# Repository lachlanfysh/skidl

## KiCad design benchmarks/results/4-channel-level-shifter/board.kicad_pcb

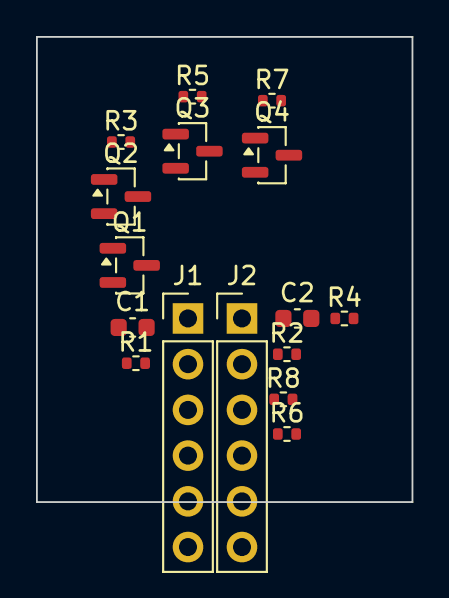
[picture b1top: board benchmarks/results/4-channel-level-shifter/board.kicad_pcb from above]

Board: 2 copper layers, 20.9 x 25.8 mm, 16 parts (0 on the bottom side), 11 nets, no tracks yet.

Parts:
C1, C2: 100nF; C_0603_1608Metric
J1: LV_HDR; PinHeader_1x06_P2.54mm_Vertical
J2: HV_HDR; PinHeader_1x06_P2.54mm_Vertical
Q1, Q2, Q3, Q4: BSS138; SOT-23
R1, R2, R3, R4, R5, R6, R7, R8: 10K; R_0402_1005Metric

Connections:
+3V3: C1.1, J1.6, Q1.1, Q2.1, Q3.1, Q4.1, R1.1, R3.1, R5.1, R7.1
+5V: C2.1, J2.6, R2.1, R4.1, R6.1, R8.1
GND: C1.2, C2.2, J1.1, J2.1
HV1: J2.2, Q1.3, R2.2
HV2: J2.3, Q2.3, R4.2
HV3: J2.4, Q3.3, R6.2
HV4: J2.5, Q4.3, R8.2
LV1: J1.2, Q1.2, R1.2
LV2: J1.3, Q2.2, R3.2
LV3: J1.4, Q3.2, R5.2
LV4: J1.5, Q4.2, R7.2

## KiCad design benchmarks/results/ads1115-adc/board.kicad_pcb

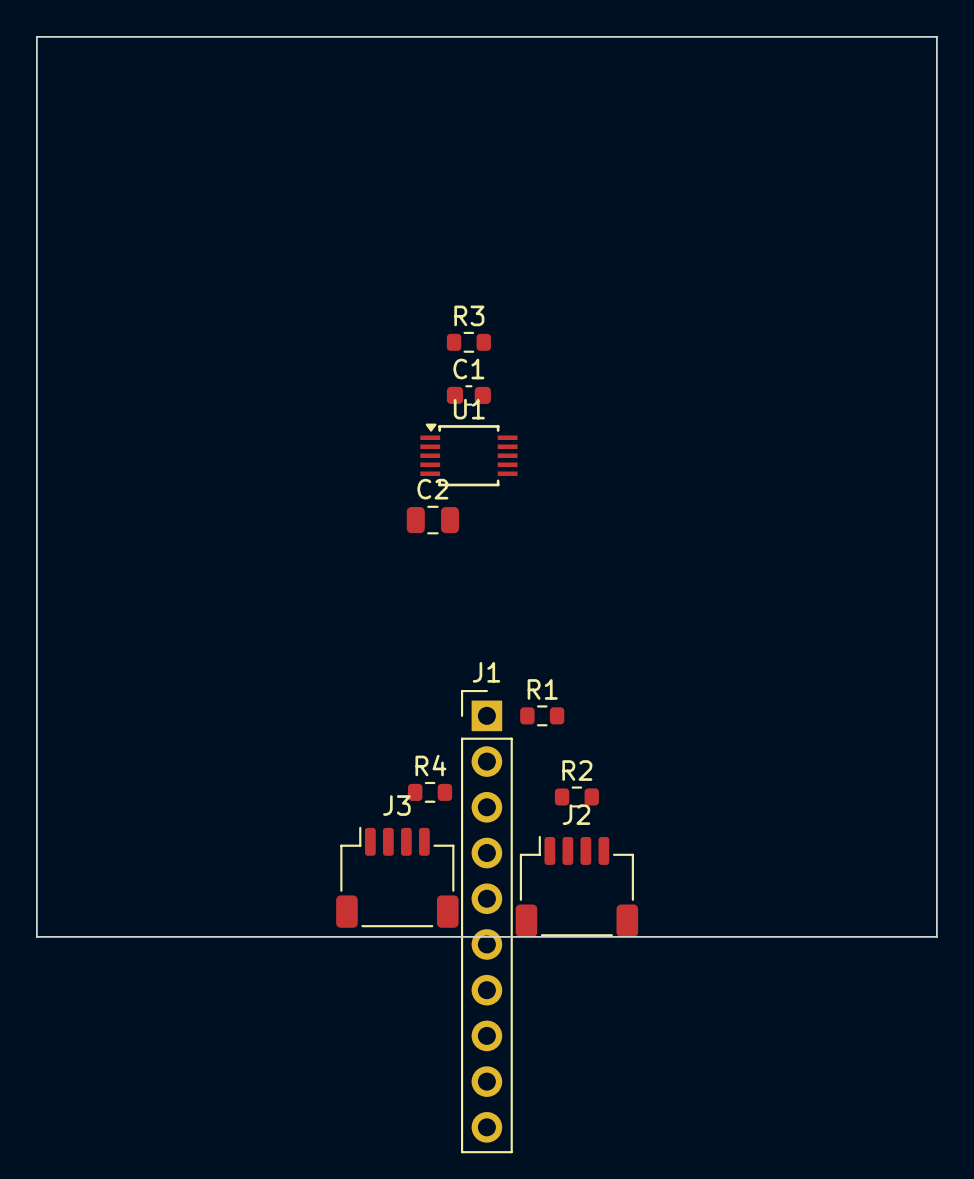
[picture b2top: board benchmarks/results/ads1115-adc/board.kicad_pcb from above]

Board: 2 copper layers, 50.0 x 50.0 mm, 10 parts (0 on the bottom side), 10 nets, no tracks yet.

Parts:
C1: 100nF; C_0603_1608Metric
C2: 10uF; C_0805_2012Metric
J1: Conn_01x10; PinHeader_1x10_P2.54mm_Vertical
J2, J3: Conn_01x04; JST_SH_SM04B-SRSS-TB_1x04-1MP_P1.00mm_Horizontal
R1, R2, R3: 10K; R_0603_1608Metric
R4: 0R; R_0603_1608Metric
U1: ADS1115IDGS; TSSOP-10_3x3mm_P0.5mm

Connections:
ADDR: J1.5, R4.1, U1.1
AIN0: J1.7, U1.4
AIN1: J1.8, U1.5
AIN2: J1.9, U1.6
AIN3: J1.10, U1.7
ALERT_RDY: J1.6, R3.2, U1.2
GND: C1.2, C2.2, J1.2, J2.1, J3.1, R4.2, U1.3
SCL: J1.3, J2.4, J3.4, R2.2, U1.10
SDA: J1.4, J2.3, J3.3, R1.2, U1.9
VDD: C1.1, C2.1, J1.1, J2.2, J3.2, R1.1, R2.1, R3.1, U1.8

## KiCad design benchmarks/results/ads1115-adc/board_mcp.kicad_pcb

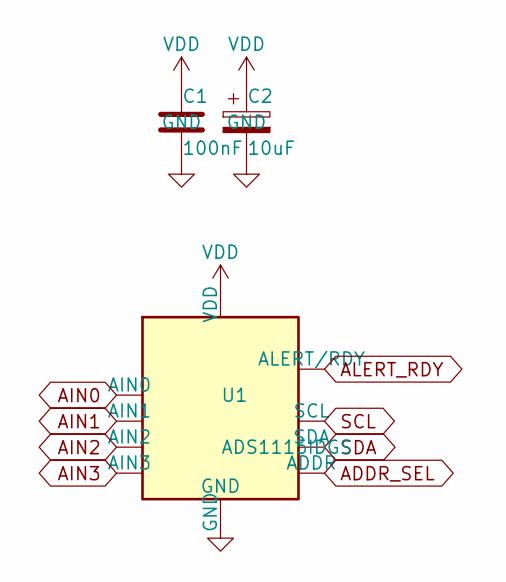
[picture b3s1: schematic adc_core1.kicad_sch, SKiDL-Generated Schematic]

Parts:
C1: 100nF; C_0402_1005Metric
C2: 10uF; C_0805_2012Metric
U1: ADS1115IDGS; TSSOP-10_3x3mm_P0.5mm

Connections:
ADDR_SEL: U1.1 (ADDR); also elsewhere on the board
AIN0: U1.4 (AIN0); also elsewhere on the board
AIN1: U1.5 (AIN1); also elsewhere on the board
AIN2: U1.6 (AIN2); also elsewhere on the board
AIN3: U1.7 (AIN3); also elsewhere on the board
ALERT_RDY: U1.2 (ALERT/RDY); also elsewhere on the board
GND: C1.2, C2.2, U1.3 (GND); also elsewhere on the board
SCL: U1.10 (SCL); also elsewhere on the board
SDA: U1.9 (SDA); also elsewhere on the board
VDD: C1.1, C2.1, U1.8 (VDD); also elsewhere on the board

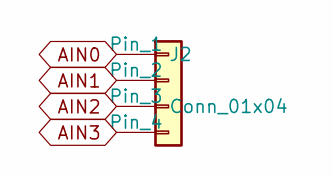
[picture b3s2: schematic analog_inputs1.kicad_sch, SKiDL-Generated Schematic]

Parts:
J2: Conn_01x04; PinHeader_1x04_P2.54mm_Vertical

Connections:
AIN0: J2.1; also elsewhere on the board
AIN1: J2.2; also elsewhere on the board
AIN2: J2.3; also elsewhere on the board
AIN3: J2.4; also elsewhere on the board

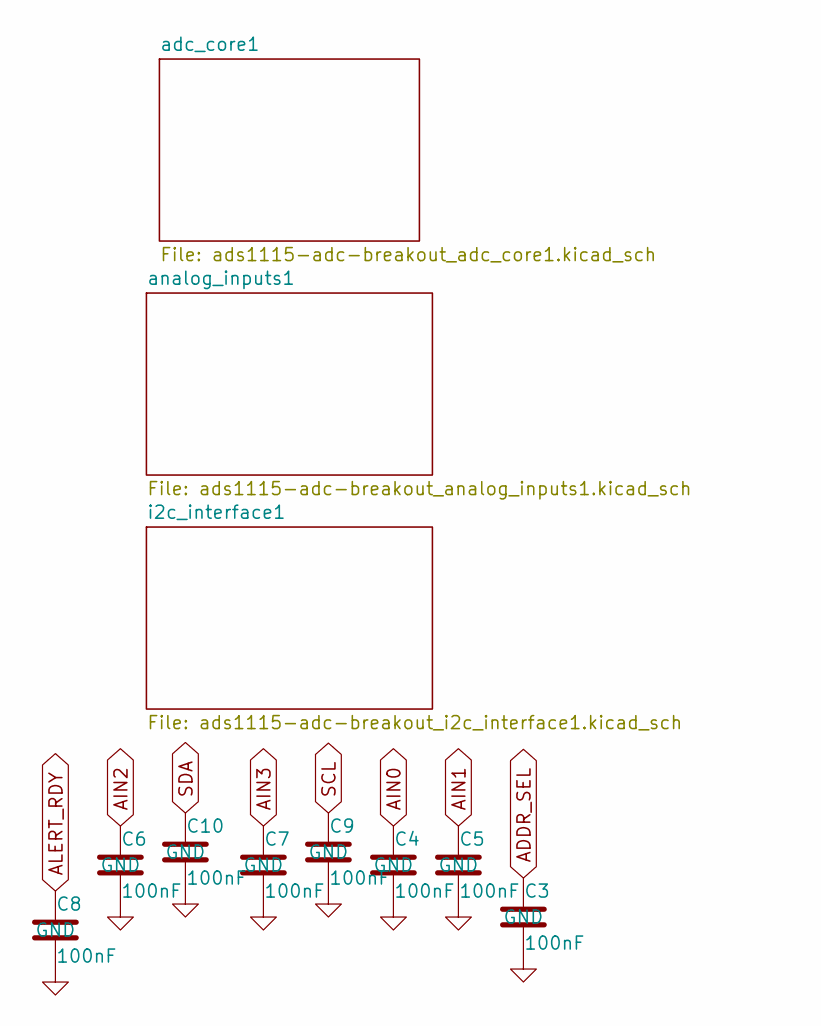
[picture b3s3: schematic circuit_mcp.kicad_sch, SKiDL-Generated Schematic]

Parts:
C3, C4, C5, C6, C7, C8, C9, C10: 100nF; C_0603_1608Metric

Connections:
ADDR_SEL: C3.1; also elsewhere on the board
AIN0: C4.1; also elsewhere on the board
AIN1: C5.1; also elsewhere on the board
AIN2: C6.1; also elsewhere on the board
AIN3: C7.1; also elsewhere on the board
ALERT_RDY: C8.1; also elsewhere on the board
GND: C3.2, C4.2, C5.2, C6.2, C7.2, C8.2, C9.2, C10.2; also elsewhere on the board
SCL: C9.1; also elsewhere on the board
SDA: C10.1; also elsewhere on the board

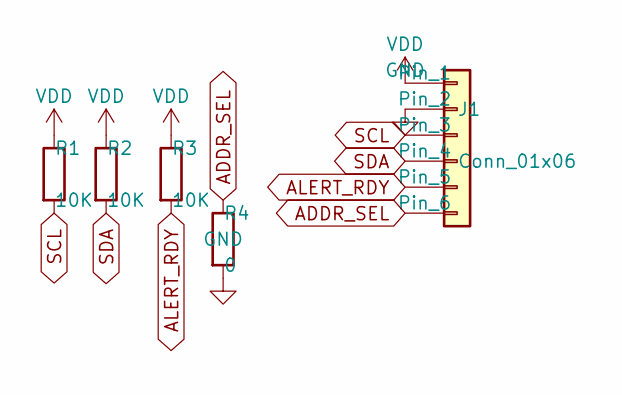
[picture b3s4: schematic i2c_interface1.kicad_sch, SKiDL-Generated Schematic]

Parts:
J1: Conn_01x06; PinHeader_1x06_P2.54mm_Vertical
R1, R2, R3: 10K; R_0402_1005Metric
R4: 0; R_0402_1005Metric

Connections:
ADDR_SEL: J1.6, R4.1; also elsewhere on the board
ALERT_RDY: J1.5, R3.2; also elsewhere on the board
GND: J1.2, R4.2; also elsewhere on the board
SCL: J1.3, R1.2; also elsewhere on the board
SDA: J1.4, R2.2; also elsewhere on the board
VDD: J1.1, R1.1, R2.1, R3.1; also elsewhere on the board

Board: 2 copper layers, 17 parts (0 on the bottom side), 10 nets, no tracks yet.

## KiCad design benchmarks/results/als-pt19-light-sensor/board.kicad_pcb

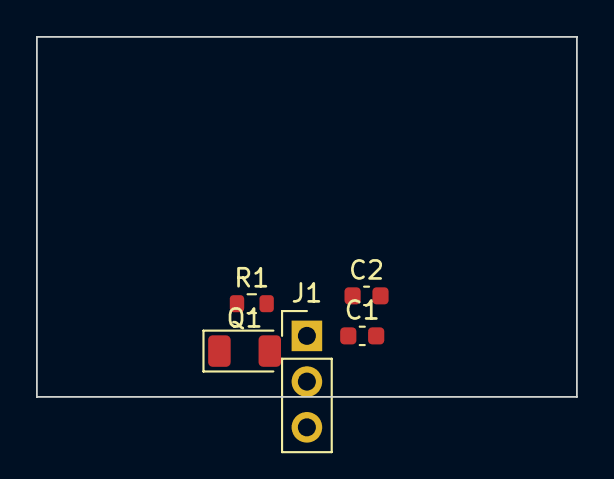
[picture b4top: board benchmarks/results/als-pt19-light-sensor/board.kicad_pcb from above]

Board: 2 copper layers, 30.0 x 20.0 mm, 5 parts (0 on the bottom side), 3 nets, no tracks yet.

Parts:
C1, C2: 100nF; C_0603_1608Metric
J1: Conn_01x03; PinHeader_1x03_P2.54mm_Vertical
Q1: ALS-PT19; LED_1206_3216Metric
R1: 10K; R_0603_1608Metric

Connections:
AOUT: C2.1, J1.3
GND: C1.2, C2.2, J1.2, Q1.2
VCC: C1.1, J1.1, R1.1

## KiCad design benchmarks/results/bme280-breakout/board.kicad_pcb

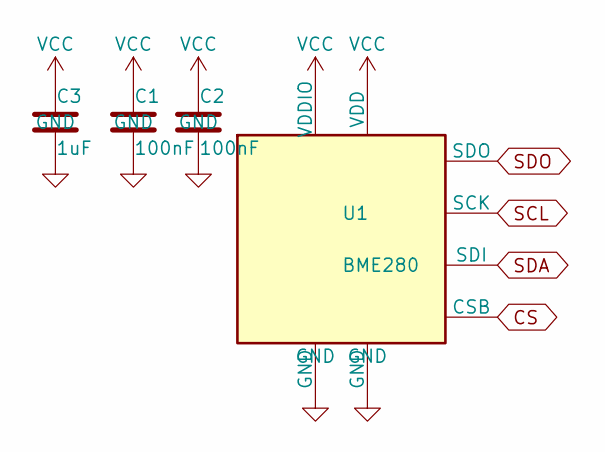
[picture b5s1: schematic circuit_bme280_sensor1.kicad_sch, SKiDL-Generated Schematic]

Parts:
C1, C2: 100nF; C_0402_1005Metric
C3: 1uF; C_0402_1005Metric
U1: BME280; Bosch_LGA-8_2.5x2.5mm_P0.65mm_ClockwisePinNumbering

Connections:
CS: U1.2 (CSB); also elsewhere on the board
GND: C1.2, C2.2, C3.2, U1.1 (GND), U1.7 (GND); also elsewhere on the board
SCL: U1.4 (SCK); also elsewhere on the board
SDA: U1.3 (SDI); also elsewhere on the board
SDO: U1.5 (SDO); also elsewhere on the board
VCC: C1.1, C2.1, C3.1, U1.6 (VDDIO), U1.8 (VDD); also elsewhere on the board

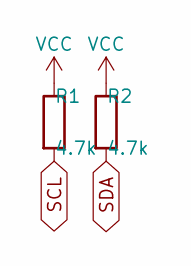
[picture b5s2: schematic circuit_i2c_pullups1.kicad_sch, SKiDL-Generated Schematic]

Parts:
R1, R2: 4.7k; R_0402_1005Metric

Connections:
SCL: R1.2; also elsewhere on the board
SDA: R2.2; also elsewhere on the board
VCC: R1.1, R2.1; also elsewhere on the board

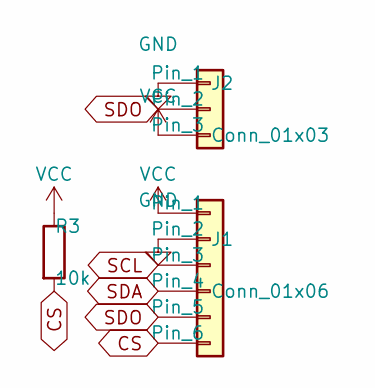
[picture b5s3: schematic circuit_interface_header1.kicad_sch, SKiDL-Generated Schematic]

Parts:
J1: Conn_01x06; PinHeader_1x06_P2.54mm_Vertical
J2: Conn_01x03; PinHeader_1x03_P2.54mm_Vertical
R3: 10k; R_0402_1005Metric

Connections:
CS: J1.6, R3.2; also elsewhere on the board
GND: J1.2, J2.1; also elsewhere on the board
SCL: J1.3; also elsewhere on the board
SDA: J1.4; also elsewhere on the board
SDO: J1.5, J2.2; also elsewhere on the board
VCC: J1.1, J2.3, R3.1; also elsewhere on the board

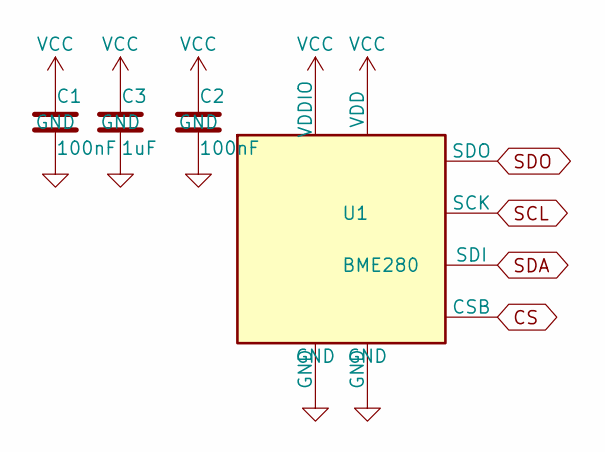
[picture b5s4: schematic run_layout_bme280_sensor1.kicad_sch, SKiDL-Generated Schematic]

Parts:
C1, C2: 100nF; C_0402_1005Metric
C3: 1uF; C_0402_1005Metric
U1: BME280; Bosch_LGA-8_2.5x2.5mm_P0.65mm_ClockwisePinNumbering

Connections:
CS: U1.2 (CSB); also elsewhere on the board
GND: C1.2, C2.2, C3.2, U1.1 (GND), U1.7 (GND); also elsewhere on the board
SCL: U1.4 (SCK); also elsewhere on the board
SDA: U1.3 (SDI); also elsewhere on the board
SDO: U1.5 (SDO); also elsewhere on the board
VCC: C1.1, C2.1, C3.1, U1.6 (VDDIO), U1.8 (VDD); also elsewhere on the board

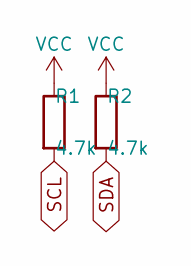
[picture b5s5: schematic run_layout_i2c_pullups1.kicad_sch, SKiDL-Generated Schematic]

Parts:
R1, R2: 4.7k; R_0402_1005Metric

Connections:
SCL: R1.2; also elsewhere on the board
SDA: R2.2; also elsewhere on the board
VCC: R1.1, R2.1; also elsewhere on the board

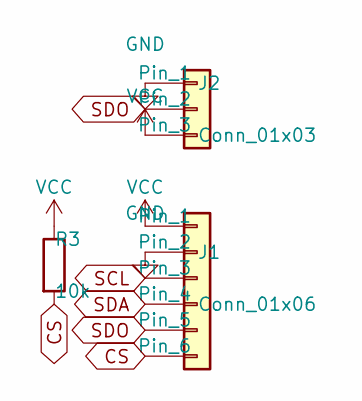
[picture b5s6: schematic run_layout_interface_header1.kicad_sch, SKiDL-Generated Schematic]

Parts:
J1: Conn_01x06; PinHeader_1x06_P2.54mm_Vertical
J2: Conn_01x03; PinHeader_1x03_P2.54mm_Vertical
R3: 10k; R_0402_1005Metric

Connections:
CS: J1.6, R3.2; also elsewhere on the board
GND: J1.2, J2.1; also elsewhere on the board
SCL: J1.3; also elsewhere on the board
SDA: J1.4; also elsewhere on the board
SDO: J1.5, J2.2; also elsewhere on the board
VCC: J1.1, J2.3, R3.1; also elsewhere on the board

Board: 2 copper layers, 9 parts (0 on the bottom side), 6 nets, no tracks yet.

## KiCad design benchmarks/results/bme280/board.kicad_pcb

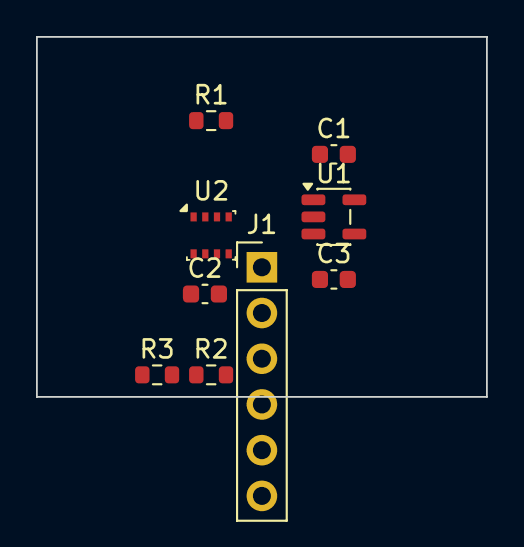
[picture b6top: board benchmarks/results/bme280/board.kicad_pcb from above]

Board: 2 copper layers, 25.0 x 20.0 mm, 9 parts (0 on the bottom side), 7 nets, no tracks yet.

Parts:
C1, C2: 1uF; C_0603_1608Metric
C3: 100nF; C_0603_1608Metric
J1: Header_1x06; PinHeader_1x06_P2.54mm_Vertical
R1, R2, R3: 10K; R_0603_1608Metric
U1: AP2112K-3.3; SOT-23-5
U2: BME280; Bosch_LGA-8_2.5x2.5mm_P0.65mm_ClockwisePinNumbering

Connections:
+3V3: C2.1, C3.1, R1.1, R2.1, R3.1, U1.5, U2.6, U2.8
CSB: J1.6, R3.2, U2.2
GND: C1.2, C2.2, C3.2, J1.2, U1.2, U2.1, U2.7
SCL: J1.3, R2.2, U2.4
SDA: J1.4, R1.2, U2.3
SDO: J1.5, U2.5
VIN: C1.1, J1.1, U1.1, U1.3

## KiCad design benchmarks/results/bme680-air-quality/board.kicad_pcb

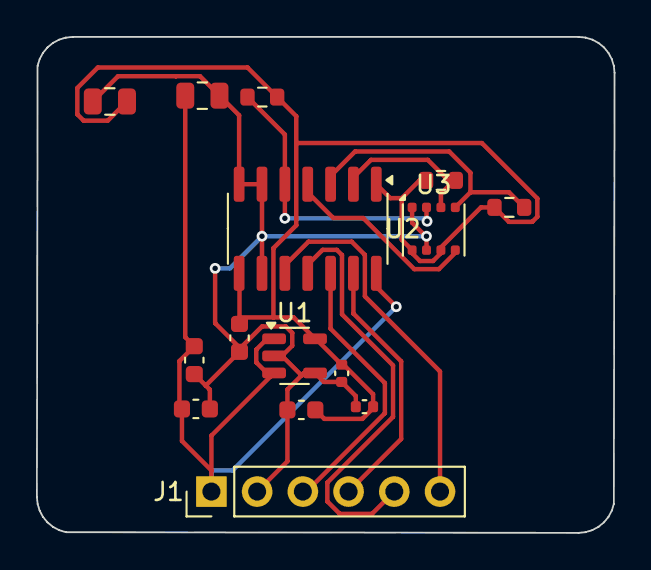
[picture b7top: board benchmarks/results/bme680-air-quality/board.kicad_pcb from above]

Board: 2 copper layers, 32.1 x 27.6 mm, 15 parts (0 on the bottom side), 11 nets.

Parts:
C1: 1uF; C_0603_1608Metric
C2, C8: 10uF; C_0805_2012Metric
C3, C4, C5: 100nF; C_0603_1608Metric
C6, C7: 100nF; C_0402_1005Metric
J1: Conn_01x06; PinHeader_1x06_P2.54mm_Vertical
R1, R2: 4.7K; R_0603_1608Metric
R3: 10K; R_0603_1608Metric
U1: AP2112K-3.3; SOT-23-5
U2: TXB0104D; SOIC-14_3.9x8.7mm_P1.27mm
U3: BME680; Bosch_LGA-8_3x3mm_P0.8mm_ClockwisePinNumbering

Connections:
+3V3: C2.1, C3.1, C4.1, C6.1, C7.1, R1.1, R2.1, R3.1, U1.5, U2.1, U2.8, U3.6, U3.8
CSB_HI: J1.6, U2.10
CSB_LO: R3.2, U2.5, U3.2
GND: C1.2, C2.2, C3.2, C4.2, C5.2, C6.2, C7.2, C8.2, J1.2, U1.2, U1.4, U2.6, U2.7, U2.9, U3.1, U3.7
SCL_HI: J1.3, U2.12
SCL_LO: R2.2, U2.3, U3.4
SDA_HI: J1.4, U2.13
SDA_LO: R1.2, U2.2, U3.3
SDO_HI: J1.5, U2.11
SDO_LO: U2.4, U3.5
VIN: C1.1, C5.1, C8.1, J1.1, U1.1, U1.3, U2.14

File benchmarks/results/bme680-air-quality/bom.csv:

Comment,Designator,Footprint,LCSC Part Number
Conn_01x06,J1,Connector_PinHeader_2.54mm:PinHeader_1x06_P2.54mm_Vertical,
AP2112K-3.3,U1,Package_TO_SOT_SMD:SOT-23-5,
1uF,C1,Capacitor_SMD:C_0603_1608Metric,
10uF,C2,Capacitor_SMD:C_0805_2012Metric,
100nF,C3,Capacitor_SMD:C_0603_1608Metric,
TXB0104D,U2,Package_SO:SOIC-14_3.9x8.7mm_P1.27mm,
100nF,C4,Capacitor_SMD:C_0603_1608Metric,
100nF,C5,Capacitor_SMD:C_0603_1608Metric,
BME680,U3,Package_LGA:Bosch_LGA-8_3x3mm_P0.8mm_ClockwisePinNumbering,
100nF,C6,Capacitor_SMD:C_0402_1005Metric,
100nF,C7,Capacitor_SMD:C_0402_1005Metric,
4.7K,R1,Resistor_SMD:R_0603_1608Metric,
4.7K,R2,Resistor_SMD:R_0603_1608Metric,
10K,R3,Resistor_SMD:R_0603_1608Metric,
10uF,C8,Capacitor_SMD:C_0805_2012Metric,

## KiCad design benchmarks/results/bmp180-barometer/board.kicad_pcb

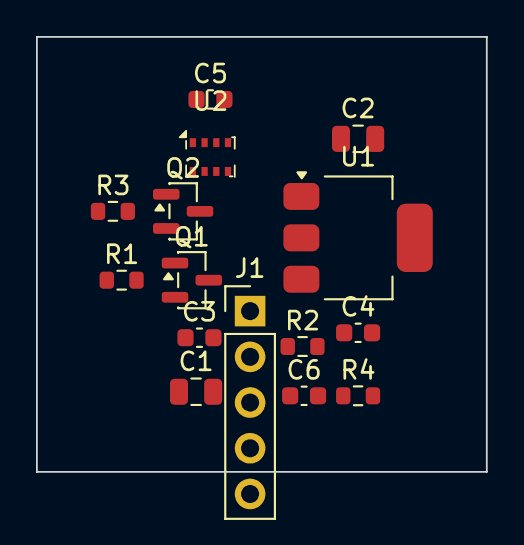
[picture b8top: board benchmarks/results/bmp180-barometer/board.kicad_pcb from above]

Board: 2 copper layers, 25.0 x 24.2 mm, 15 parts (0 on the bottom side), 7 nets, no tracks yet.

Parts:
C1, C2: 10uF; C_0805_2012Metric
C3, C4, C5, C6: 100nF; C_0603_1608Metric
J1: Conn_01x05; PinHeader_1x05_P2.54mm_Vertical
Q1, Q2: BSS138; SOT-23
R1, R2, R3, R4: 10K; R_0603_1608Metric
U1: AMS1117-3.3; SOT-223-3_TabPin2
U2: BMP280; Bosch_LGA-8_2x2.5mm_P0.65mm_ClockwisePinNumbering

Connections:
+3V3: C2.1, C3.1, C4.1, C5.1, J1.5, Q1.1, Q2.1, R1.1, R3.1, U1.2, U2.2, U2.6, U2.8
+5V: C1.1, C6.1, J1.1, R2.1, R4.1, U1.3
GND: C1.2, C2.2, C3.2, C4.2, C5.2, C6.2, J1.2, U1.1, U2.1, U2.5, U2.7
SCL_3V3: Q2.2, R3.2, U2.4
SCL_5V: J1.3, Q2.3, R4.2
SDA_3V3: Q1.2, R1.2, U2.3
SDA_5V: J1.4, Q1.3, R2.2

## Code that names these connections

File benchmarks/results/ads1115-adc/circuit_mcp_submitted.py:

"""
ADS1115 ADC Breakout - SKiDL code submitted to MCP server.
Run ID: db77d7983152 (job: b5caa6eb0f7b)
Status: layout complete, 1 overlap (J1/C1), schematic + PCB artifacts generated.
"""
from skidl import *

# Power rails
vdd = Net("VDD"); vdd.drive = POWER
gnd = Net("GND"); gnd.drive = POWER

# I2C bus
scl = Net("SCL")
sda = Net("SDA")

# Analog inputs
ain0 = Net("AIN0")
ain1 = Net("AIN1")
ain2 = Net("AIN2")
ain3 = Net("AIN3")

# Misc nets
alert = Net("ALERT_RDY")
addr_net = Net("ADDR_SEL")

@subcircuit
def adc_core(vdd, gnd, scl, sda, ain0, ain1, ain2, ain3, alert, addr_net):
    # ADS1115 ADC IC (VSSOP-10)
    u1 = Part("Analog_ADC", "ADS1115IDGS",
              footprint="Package_SO:TSSOP-10_3x3mm_P0.5mm")
    vdd  += u1["VDD"]
    gnd  += u1["GND"]
    scl  += u1["SCL"]
    sda  += u1["SDA"]
    ain0 += u1["AIN0"]
    ain1 += u1["AIN1"]
    ain2 += u1["AIN2"]
    ain3 += u1["AIN3"]
    alert    += u1["ALERT/RDY"]
    addr_net += u1["ADDR"]

    # 100nF decoupling cap on VDD (auto-detected by placer)
    c1 = Part("Device", "C", value="100nF",
              footprint="Capacitor_SMD:C_0402_1005Metric")
    vdd += c1[1]
    gnd += c1[2]

    # 10uF bulk cap on VDD
    c2 = Part("Device", "C_Polarized", value="10uF",
              footprint="Capacitor_SMD:C_0805_2012Metric")
    vdd += c2[1]
    gnd += c2[2]

@subcircuit
def i2c_interface(vdd, gnd, scl, sda, alert, addr_net):
    # I2C pull-ups
    r_scl = Part("Device", "R", value="10K",
                 footprint="Resistor_SMD:R_0402_1005Metric")
    r_sda = Part("Device", "R", value="10K",
                 footprint="Resistor_SMD:R_0402_1005Metric")
    vdd += r_scl[1]; scl += r_scl[2]
    vdd += r_sda[1]; sda += r_sda[2]

    # ALERT/RDY pull-up
    r_alert = Part("Device", "R", value="10K",
                   footprint="Resistor_SMD:R_0402_1005Metric")
    vdd += r_alert[1]; alert += r_alert[2]

    # ADDR select: 0-ohm resistor to GND -> I2C address 0x48
    # Reflow to VDD pad for 0x49
    r_addr = Part("Device", "R", value="0",
                  footprint="Resistor_SMD:R_0402_1005Metric")
    addr_net += r_addr[1]; gnd += r_addr[2]

    # I2C + Power header (6-pin): VDD, GND, SCL, SDA, ALERT, ADDR_SEL
    j1 = Part("Connector_Generic", "Conn_01x06",
               footprint="Connector_PinHeader_2.54mm:PinHeader_1x06_P2.54mm_Vertical")
    vdd      += j1[1]
    gnd      += j1[2]
    scl      += j1[3]
    sda      += j1[4]
    alert    += j1[5]
    addr_net += j1[6]

@subcircuit
def analog_inputs(ain0, ain1, ain2, ain3):
    # Analog inputs header (4-pin): AIN0, AIN1, AIN2, AIN3
    j2 = Part("Connector_Generic", "Conn_01x04",
               footprint="Connector_PinHeader_2.54mm:PinHeader_1x04_P2.54mm_Vertical")
    ain0 += j2[1]
    ain1 += j2[2]
    ain2 += j2[3]
    ain3 += j2[4]

adc_core(vdd, gnd, scl, sda, ain0, ain1, ain2, ain3, alert, addr_net)
i2c_interface(vdd, gnd, scl, sda, alert, addr_net)
analog_inputs(ain0, ain1, ain2, ain3)
